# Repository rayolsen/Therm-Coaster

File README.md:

# Temperature-Coaster

The idea is simple: create a drink coaster which indicates what temperature a drink placed on it is. whether hot or cold, by turning red or blue. The ideal use for this is to be able to tell if your coffee has gone cold.  

I plan on using ATTiny85 do the work, since it should run on 3v 
CR2023 is 3v and should have enough mA to power it and some SK6812 / 5050 RGB LEDS
And a thermresistor will sense the temp, obviously.

The end game is to dip the board in resin to waterproof and protect the board making into an actual coaster.
The bottom side of the board will have the battery holder and pads to program the Attiny85.  I plan on leaving a recess in the epoxy to allow battery access.  I may make a recess for the pads for debugging,  but i plan to work out the code and kinks before putting it in resin

---
This is intended to be an Entry for the [HackaDay Coin Cell Challenge](https://hackaday.io/contest/28283-coin-cell-challenge)

Keeping in with the rules of the challenge, i've added the board to [OSHPark](https://oshpark.com/shared_projects/DYg7IxAX) 

<a href="https://oshpark.com/shared_projects/DYg7IxAX"></img></a>

Future add-ons may include some IoT for notifying when the drink reaches a certain temp or something

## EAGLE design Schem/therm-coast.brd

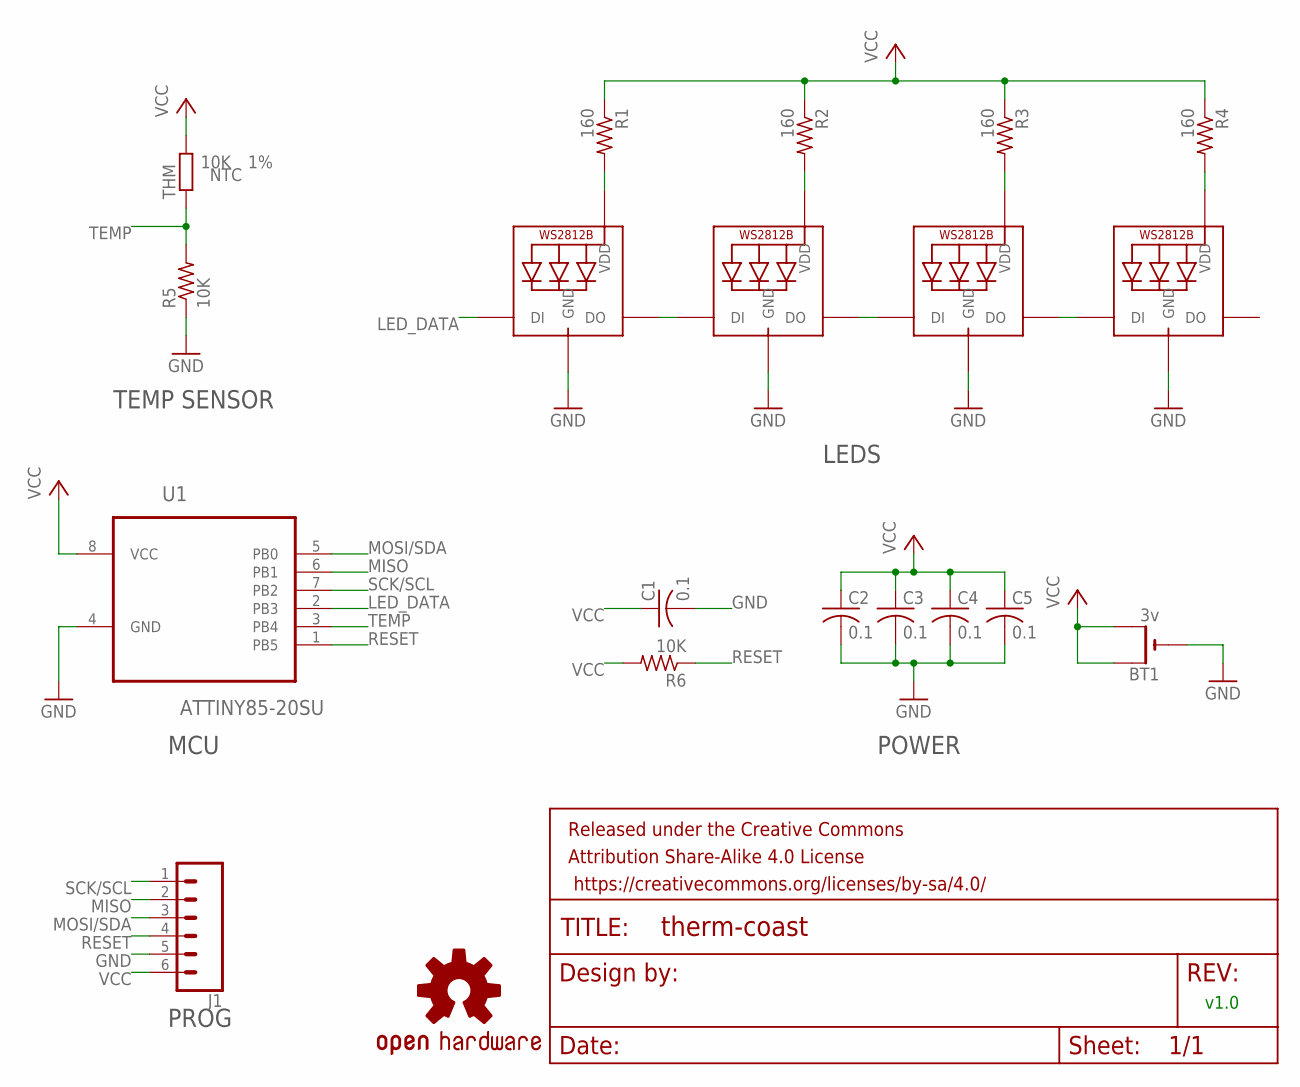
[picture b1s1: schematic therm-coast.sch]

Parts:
BT1: 3v; CR2032-SMD
C1, C2, C3, C4, C5: 0.1; C0805
FRAME1: FRAME-LETTER; CREATIVE_COMMONS
J1: CONN_06SMD-FEMALE-V2; 1X06-SMD-FEMALE
LED1, LED2, LED3, LED4: WS2812B5050; WS2812B
LOGO1: OSHW-LOGOL; OSHW-LOGO-L
R1, R2, R3, R4: 160; R0805
R5, R6: 10K; R0805
THM: 10K; R0805; TOLERANCE 1%
U1: ATTINY85-20SU; SOIC127P798X216-8N

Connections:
GND: BT1.-, C1.2, C2.2, C3.2, C4.2, C5.2, J1.5, LED1.3-GND (GND), LED2.3-GND (GND), LED3.3-GND (GND), LED4.3-GND (GND), R5.1, U1.4 (GND)
LED_DATA: LED1.4-DIN (DI), U1.2 (PB3)
MISO: J1.2, U1.6 (PB1)
MOSI/SDA: J1.3, U1.5 (PB0)
unnamed: LED1.1-VDD (VDD), R1.2
unnamed: LED2.1-VDD (VDD), R2.2
unnamed: LED3.1-VDD (VDD), R3.2
unnamed: LED4.1-VDD (VDD), R4.2
unnamed: LED1.2-DOUT (DO), LED2.4-DIN (DI)
unnamed: LED2.2-DOUT (DO), LED3.4-DIN (DI)
unnamed: LED3.2-DOUT (DO), LED4.4-DIN (DI)
RESET: J1.4, R6.1, U1.1 (PB5)
SCK/SCL: J1.1, U1.7 (PB2)
TEMP: R5.2, THM.1, U1.3 (PB4)
VCC: BT1.+$1 (+), BT1.+$2 (+1), C1.1, C2.1, C3.1, C4.1, C5.1, J1.6, R1.1, R2.1, R3.1, R4.1, R6.2, THM.2, U1.8 (VCC)

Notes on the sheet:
v1.0
TEMP SENSOR
MCU
PROG
LEDS
POWER

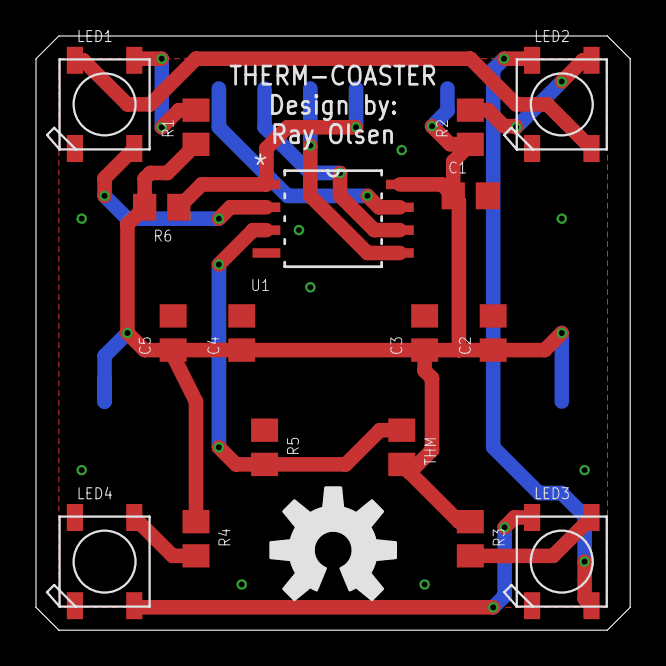
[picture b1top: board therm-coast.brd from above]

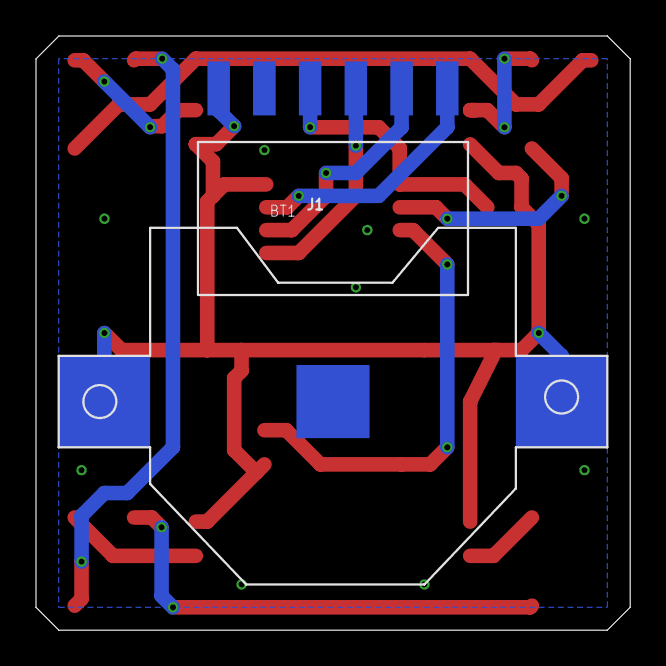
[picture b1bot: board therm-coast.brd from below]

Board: 2 copper layers, 33.0 x 33.0 mm, 21 parts (2 on the bottom side), 15 nets.

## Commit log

2017-12-13 schematic creation
2017-12-14 Readme update
2017-12-15 Schematic Design
    Added major components including LEDs, Thermsistor and some power regulation
2017-12-19 board design
2017-12-21 Board Placement and Routing updates
2017-12-21 Rev 1.0
    Better Route and Placement, Silks
2017-12-22 Fix #1
    Updates to fixz issue with vias exposed to ground plane
2017-12-22 Fix #1.1
    few fixes forgotten in last push
2017-12-26 minor fixes
2017-12-26 Cleaned up for entry
2017-12-27 Graphics!
2018-01-02 3d render mock up
2018-10-04 Oragnizing

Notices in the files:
parts and their libraries:
SparkFun-Connectors: Licensing: Creative Commons ShareAlike 4.0 International - https://creativecommons.org/licenses/by-sa/4.0
SparkFun-Aesthetics: Released under the Creative Commons Attribution Share-Alike 4.0 License
SparkFun-Aesthetics: https://creativecommons.org/licenses/by-sa/4.0
